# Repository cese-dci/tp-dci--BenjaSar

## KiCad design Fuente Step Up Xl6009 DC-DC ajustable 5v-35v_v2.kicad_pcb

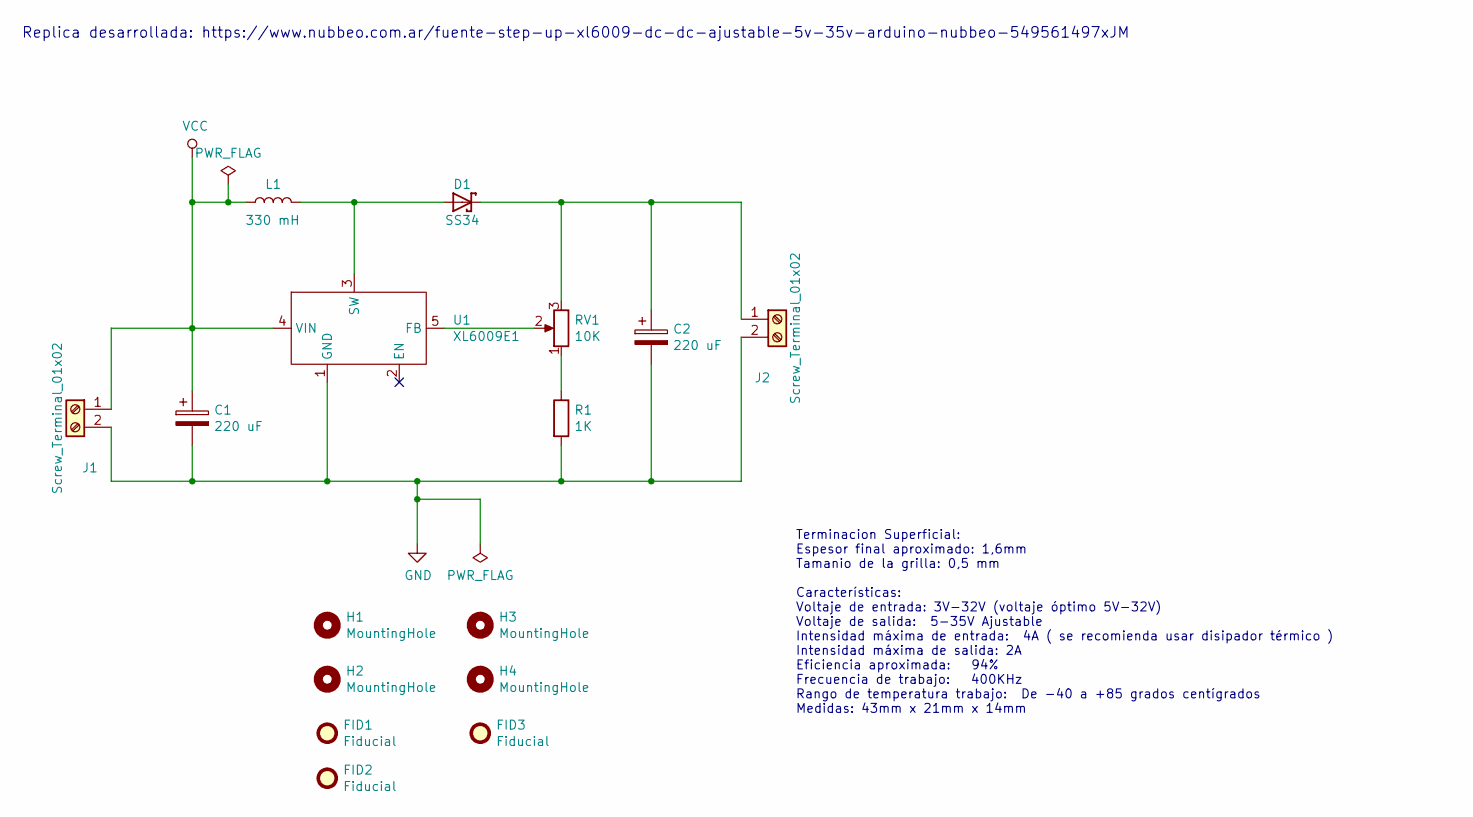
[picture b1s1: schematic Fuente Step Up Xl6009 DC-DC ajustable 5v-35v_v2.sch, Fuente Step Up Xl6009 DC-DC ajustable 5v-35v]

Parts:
C1, C2: 220 uF; CP_Elec_10x10
D1: SS34; SMB
FID1, FID2, FID3: Fiducial; Fiducial_0.5mm_Mask1.5mm
H1, H2, H3, H4: MountingHole; MountingHole_3.2mm_M3
J1, J2: Screw_Terminal_01x02; TerminalBlock_Altech_AK300-2_P5.00mm
L1: 330 mH; L_12x12mm_H8mm
R1: 1K; R_1806_4516Metric
RV1: 10K; Potentiometer_Bourns_3296W_Vertical
U1: XL6009E1; TO263-5

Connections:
GND: C1.2, C2.2, J1.2, J2.2, R1.2, U1.1 (GND)
unnamed: C2.1, D1.C, J2.1, RV1.3
unnamed: D1.A, L1.2, U1.3 (SW)
unnamed: R1.1, RV1.1
unnamed: RV1.2, U1.5 (FB)
VCC: C1.1, J1.1, L1.1, U1.4 (VIN)

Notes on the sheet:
Terminacion Superficial: Espesor final aproximado: 1,6mm Tamanio de la grilla: 0,5 mm Características: Voltaje de entrada: 3V-32V (voltaje óptimo 5V-32V) Voltaje de salida: 5-35V Ajustable Intensidad máxima de entrada: 4A ( se recomienda usar disipador térmico ) Intensidad máxima de salida: 2A Efic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
Replica desarrollada: https://www.nubbeo.com.ar/fuente-step-up-xl6009-dc-dc-ajustable-5v-35v-arduino-nubbeo-549561497xJM

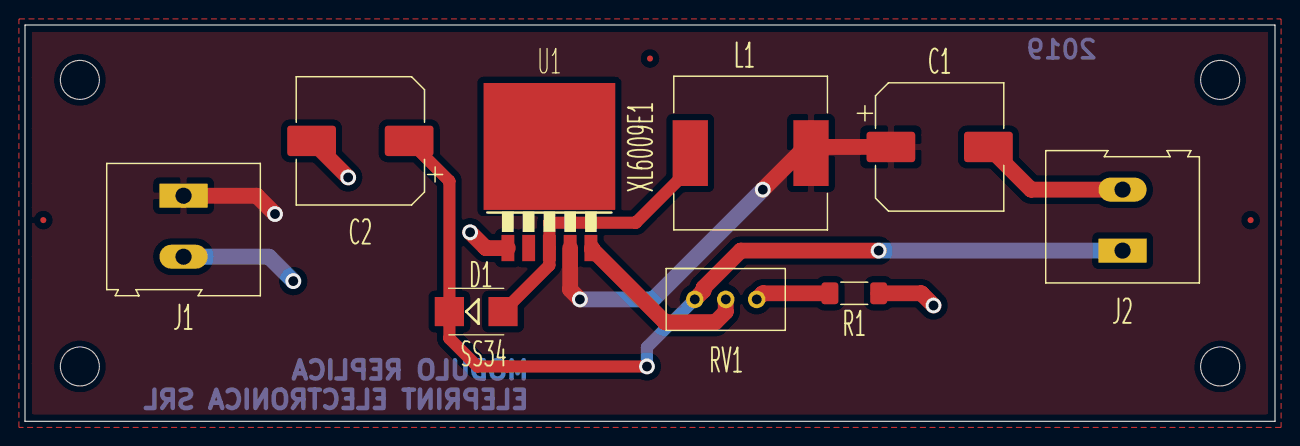
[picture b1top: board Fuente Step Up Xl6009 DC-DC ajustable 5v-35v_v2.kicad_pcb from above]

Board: 2 copper layers, 102.5 x 32.5 mm, 16 parts (0 on the bottom side), 6 nets.

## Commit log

2019-09-22 Primer commit
2019-10-02 Se realizan modificaciones sugeridas por el revisor
2019-10-06 Se agregaron las carpetas Doc e Info
2019-10-10 Se anadieron los footprints del regulador XL6009 y del potenciometro TH modelo 3296W
2019-10-20 Se creo pcb y se hicieron modificaciones de acuerdo a recomendaciones del docente
2019-10-21 Se modificaron las posiciones de los componentes de acuerdo a la recomencadion del companiero y se rutearon nuevamente algunas pistas
2019-10-24 Se agregaron los codigos de los productos y se efectuaron las recomendaciones sugeridas por el companiero
2019-10-25 Se acomodaron componentes y acortaron rutas
